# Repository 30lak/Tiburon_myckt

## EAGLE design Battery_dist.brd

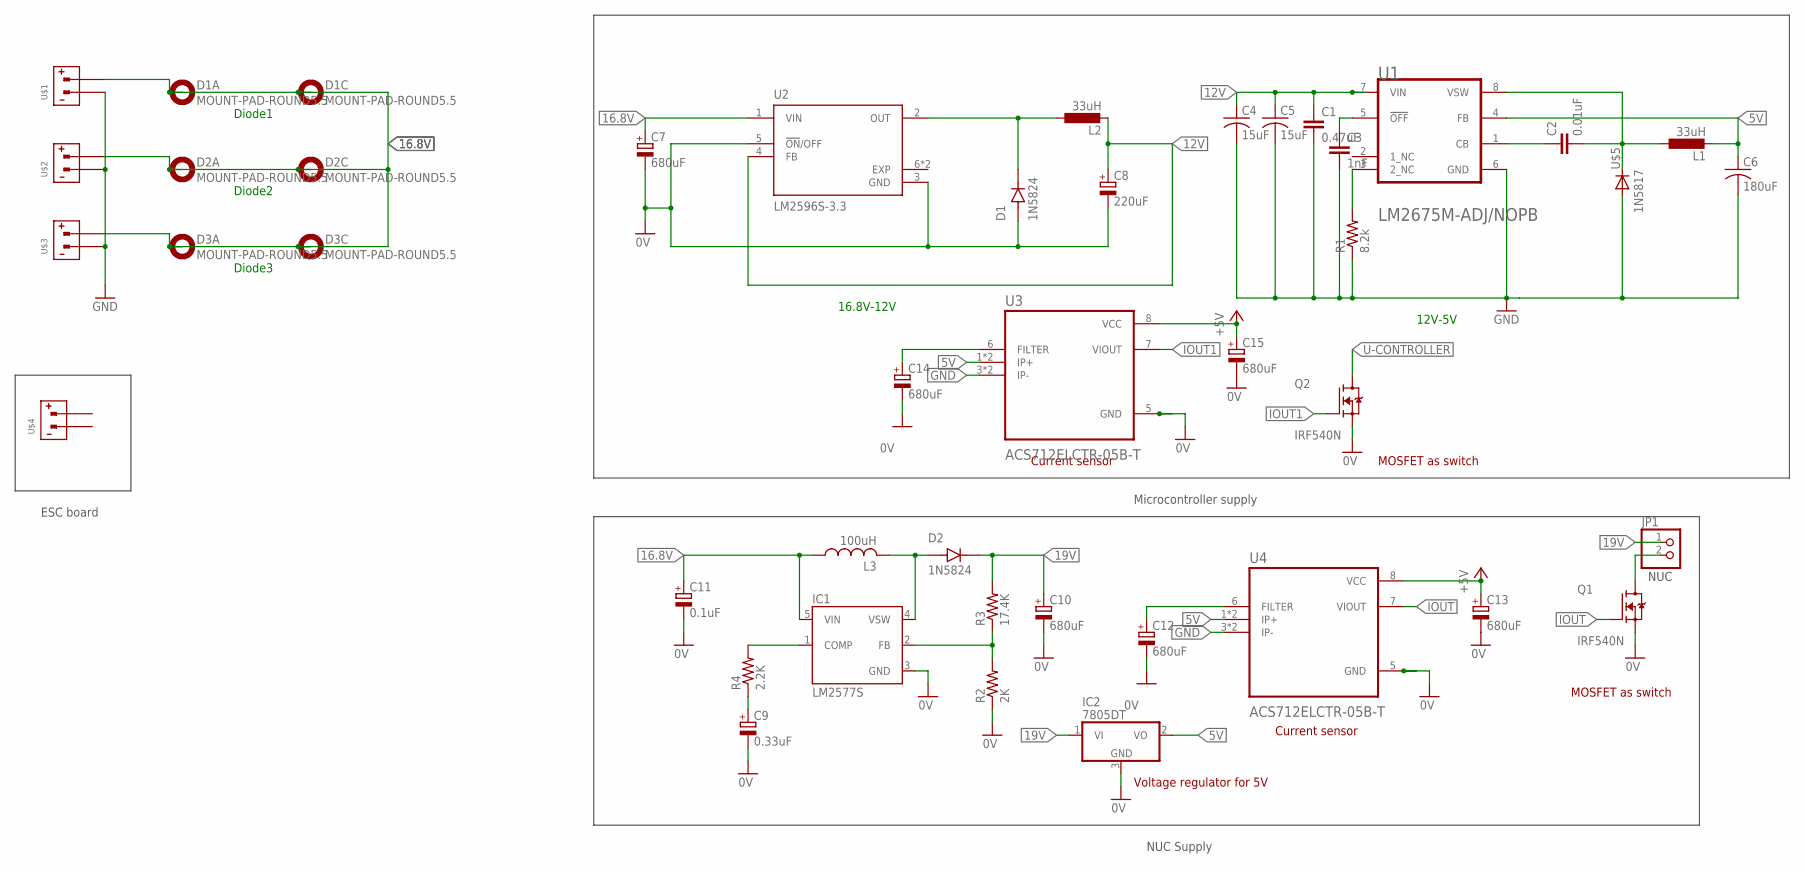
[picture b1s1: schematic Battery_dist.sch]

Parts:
C1: 0.47uF; C025-024X044
C2: 0.01uF; C025-024X044
C3: 1nF; C025-024X044
C4, C5: 15uF; C0805K
C6: 180uF; C0805K
C7, C10, C12, C13, C14, C15: 680uF; CAP4
C8: 220uF; CAP4
C9: 0.33uF; CAP4
C11: 0.1uF; CAP4
D1, D2: 1N5824; DIOAD1898W129L762D1143
D1A, D1C, D2A, D2C, D3A, D3C: MOUNT-PAD-ROUND5.5; 5,5-PAD
IC1: LM2577S; TO263-5
IC2: 7805DT; TO252
JP1: PINHD-1X2; 1X02
L1, L2: 33uH; PIS2816
L3: 100uH; L2825P
Q1, Q2: IRF540N; TO254P1054X469X1930-3
R1: 8.2k; M1206
R2: 2K; M1206
R3: 17.4K; M1206
R4: 2.2K; M1206
U1: TI_NATIONAL_SEMICONDUCTOR_LM2675M-ADJ-NOPBTI_NATI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; TI_NATIONAL_SEMICONDUCTOR_LM2675M-ADJ-NOPB_0
U2: LM2596S-3.3; VREG_LM2596S-3.3
U3, U4: ACS712ELCTR-05B-T; SOIC127P600X175-8N
U$1, U$2, U$3: XT60PW-M
U$4: XT60PW-F
U$5: 1N5817; DO41-10

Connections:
0V: C7.-, C8.-, C9.-, C10.-, C11.-, C12.-, C13.-, C14.-, C15.-, D1.A, IC1.3 (GND), IC2.3 (GND), Q1.3 (S), Q2.3 (S), R2.1, U2.3 (GND), U2.5 (!ON!/OFF), U3.5 (GND), U4.5 (GND)
5V: C6.1, IC2.2 (VO), JP1.2, L1.2, Q1.2 (D), U1.4 (FB), U3.1 (IP+), U3.2 (IP+), U4.1 (IP+), U4.2 (IP+)
12V: C1.1, C4.1, C5.1, C8.+, L2.2, U1.7 (VIN), U2.4 (FB)
16.8V: C7.+, C11.+, D1A.B5,5, D1C.B5,5, D2A.B5,5, D2C.B5,5, D3A.B5,5, D3C.B5,5, IC1.5 (VIN), L3.1, U2.1 (VIN), U$1.+VE, U$2.+VE, U$3.+VE
19V: C10.+, D2.C (K), IC2.1 (VI), JP1.1, R3.2
+5V: C13.+, C15.+, U3.8 (VCC), U4.8 (VCC)
EXP: U2.6 (EXP), U2.7 (EXP)
GND: C1.2, C3.2, C4.2, C5.2, C6.2, R1.1, U1.6 (GND), U3.3 (IP-), U3.4 (IP-), U4.3 (IP-), U4.4 (IP-), U$1.-VE, U$2.-VE, U$3.-VE, U$5.A
IOUT: Q1.1 (G), U4.7 (VIOUT)
IOUT1: Q2.1 (G), U3.7 (VIOUT)
unnamed: D1.C (K), L2.1, U2.2 (OUT)
unnamed: C3.1, U1.5 (!OFF!)
unnamed: R1.2, U1.3 (2_NC)
unnamed: C2.1, U1.1 (CB)
unnamed: C2.2, L1.1, U1.8 (VSW), U$5.C
unnamed: IC1.2 (FB), R2.2, R3.1
unnamed: C14.+, U3.6 (FILTER)
unnamed: D2.A, IC1.4 (VSW), L3.2
unnamed: C9.+, R4.1
unnamed: IC1.1 (COMP), R4.2
unnamed: C12.+, U4.6 (FILTER)
U-CONTROLLER: Q2.2 (D)

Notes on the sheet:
Diode1
Diode2
Diode3
12V-5V
16.8V-12V
ESC board
Microcontroller supply
NUC
NUC Supply
Current sensor
MOSFET as switch
Voltage regulator for 5V

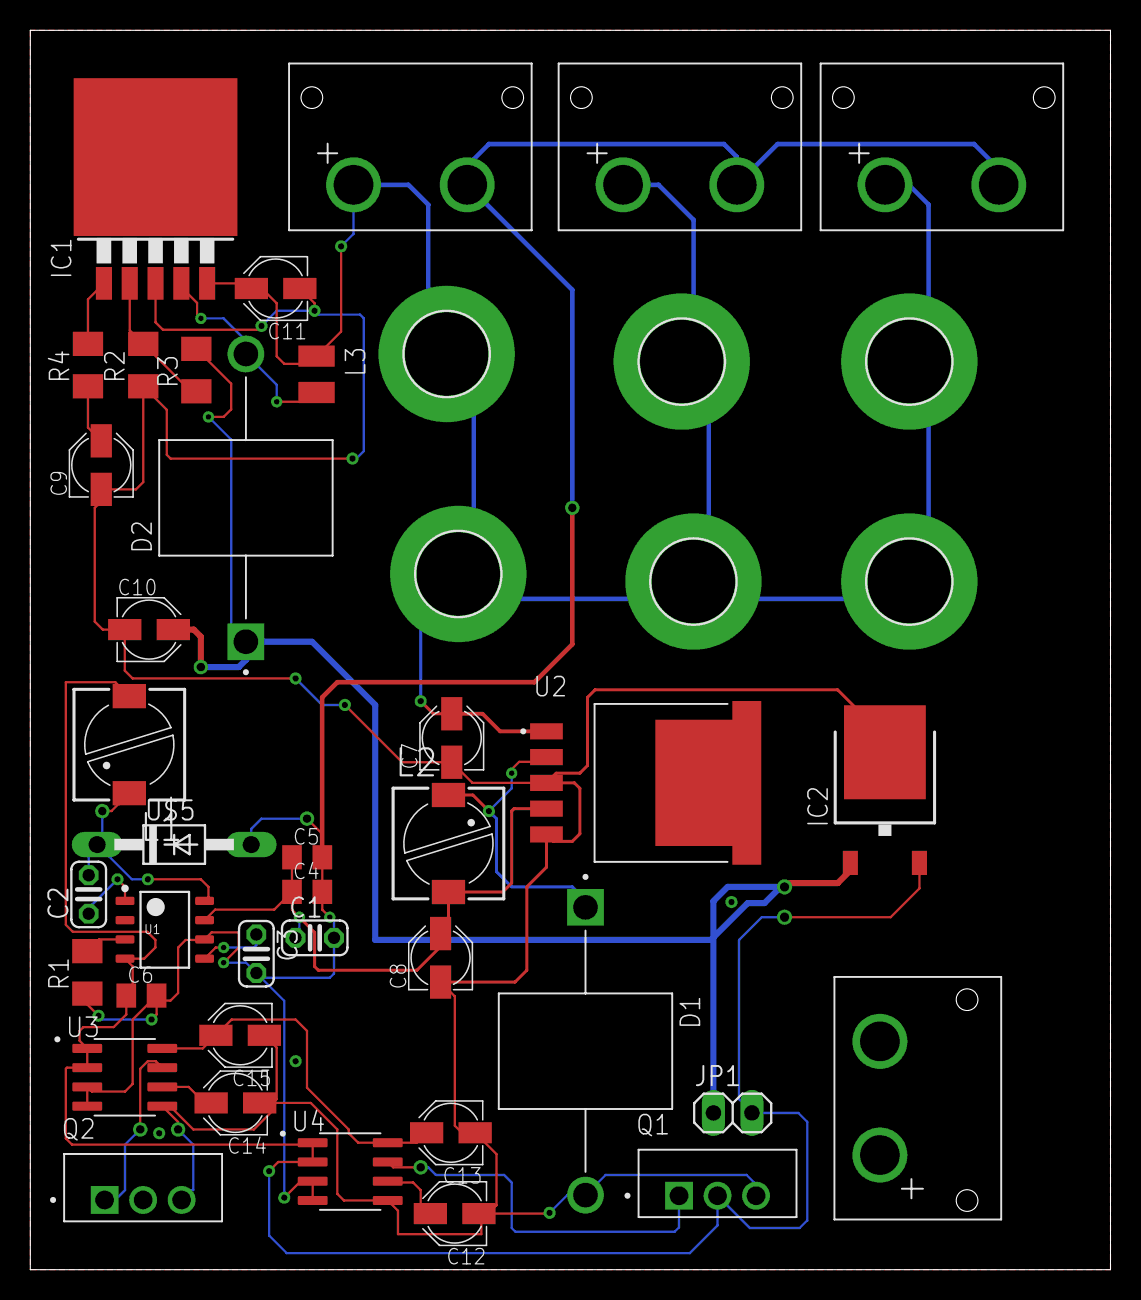
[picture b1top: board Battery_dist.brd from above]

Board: 2 copper layers, 71.2 x 81.8 mm, 44 parts (0 on the bottom side), 21 nets.
